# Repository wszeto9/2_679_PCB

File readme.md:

# 2.679/2.007 Carrier Board
High Power throughput board for the 2.007 "Legacy" Robotics Competiton @ MIT, Spring 2022

[Interactive BOM](https://htmlpreview.github.io/?https://raw.githubusercontent.com/wszeto9/2_679_PCB/main/bom/ibom.html)

<h2> Features:</h2>
<ul>
<li>20A socketable fused input</li>
<li>Reverse polarity protection with warning lights and buzzer to alert incorrect wiring</li>
<li>9V USB-C Power Delivery Input to run off larger battery packs during testing</li>
<li>Protection Circuit to prevent USB-C from backcharging battery</li>
<li>Motor headers with 8.2V Output</li>
<li>Adjustable Servo voltage from 5V to Battery voltage</li>
<li>6A Syncronous Buck converter to reduce the voltage difference between the servo voltage and battery boltage</li>
<li>16 Actuator Ports (8 individually controllable)</li>
<li>Comparator Circuit for light based start signal, directly wired to an Arduino Interrupt</li>
<li>Mechanically Adjustable trigger point for photoresistor interrupt input</li>
<li>8-channel RC controller input for compatability with Gobilda RC Receiver</li>
<li>MPU6050 and LSM6DS33 Header for heading measurements with interrupt pins connected to D2</li>
<li> 5V and 3.3V I2C headers for a multitude of sensor inputs</li>
<li>ARGB Debugging LEDs to offer more variations of debugging signals</li>
<li>ARGB Header to decorate robot in <i><b>light</b></i></li>
<li>Breakout boards for Hall Effect Sensors, In-Line current sensors, and I/O Breakout boards </li>
<li>Fun Silkscreen messages for my favorite professors </li>
</ul>

PCBA

Top

Top Unpopulated Board

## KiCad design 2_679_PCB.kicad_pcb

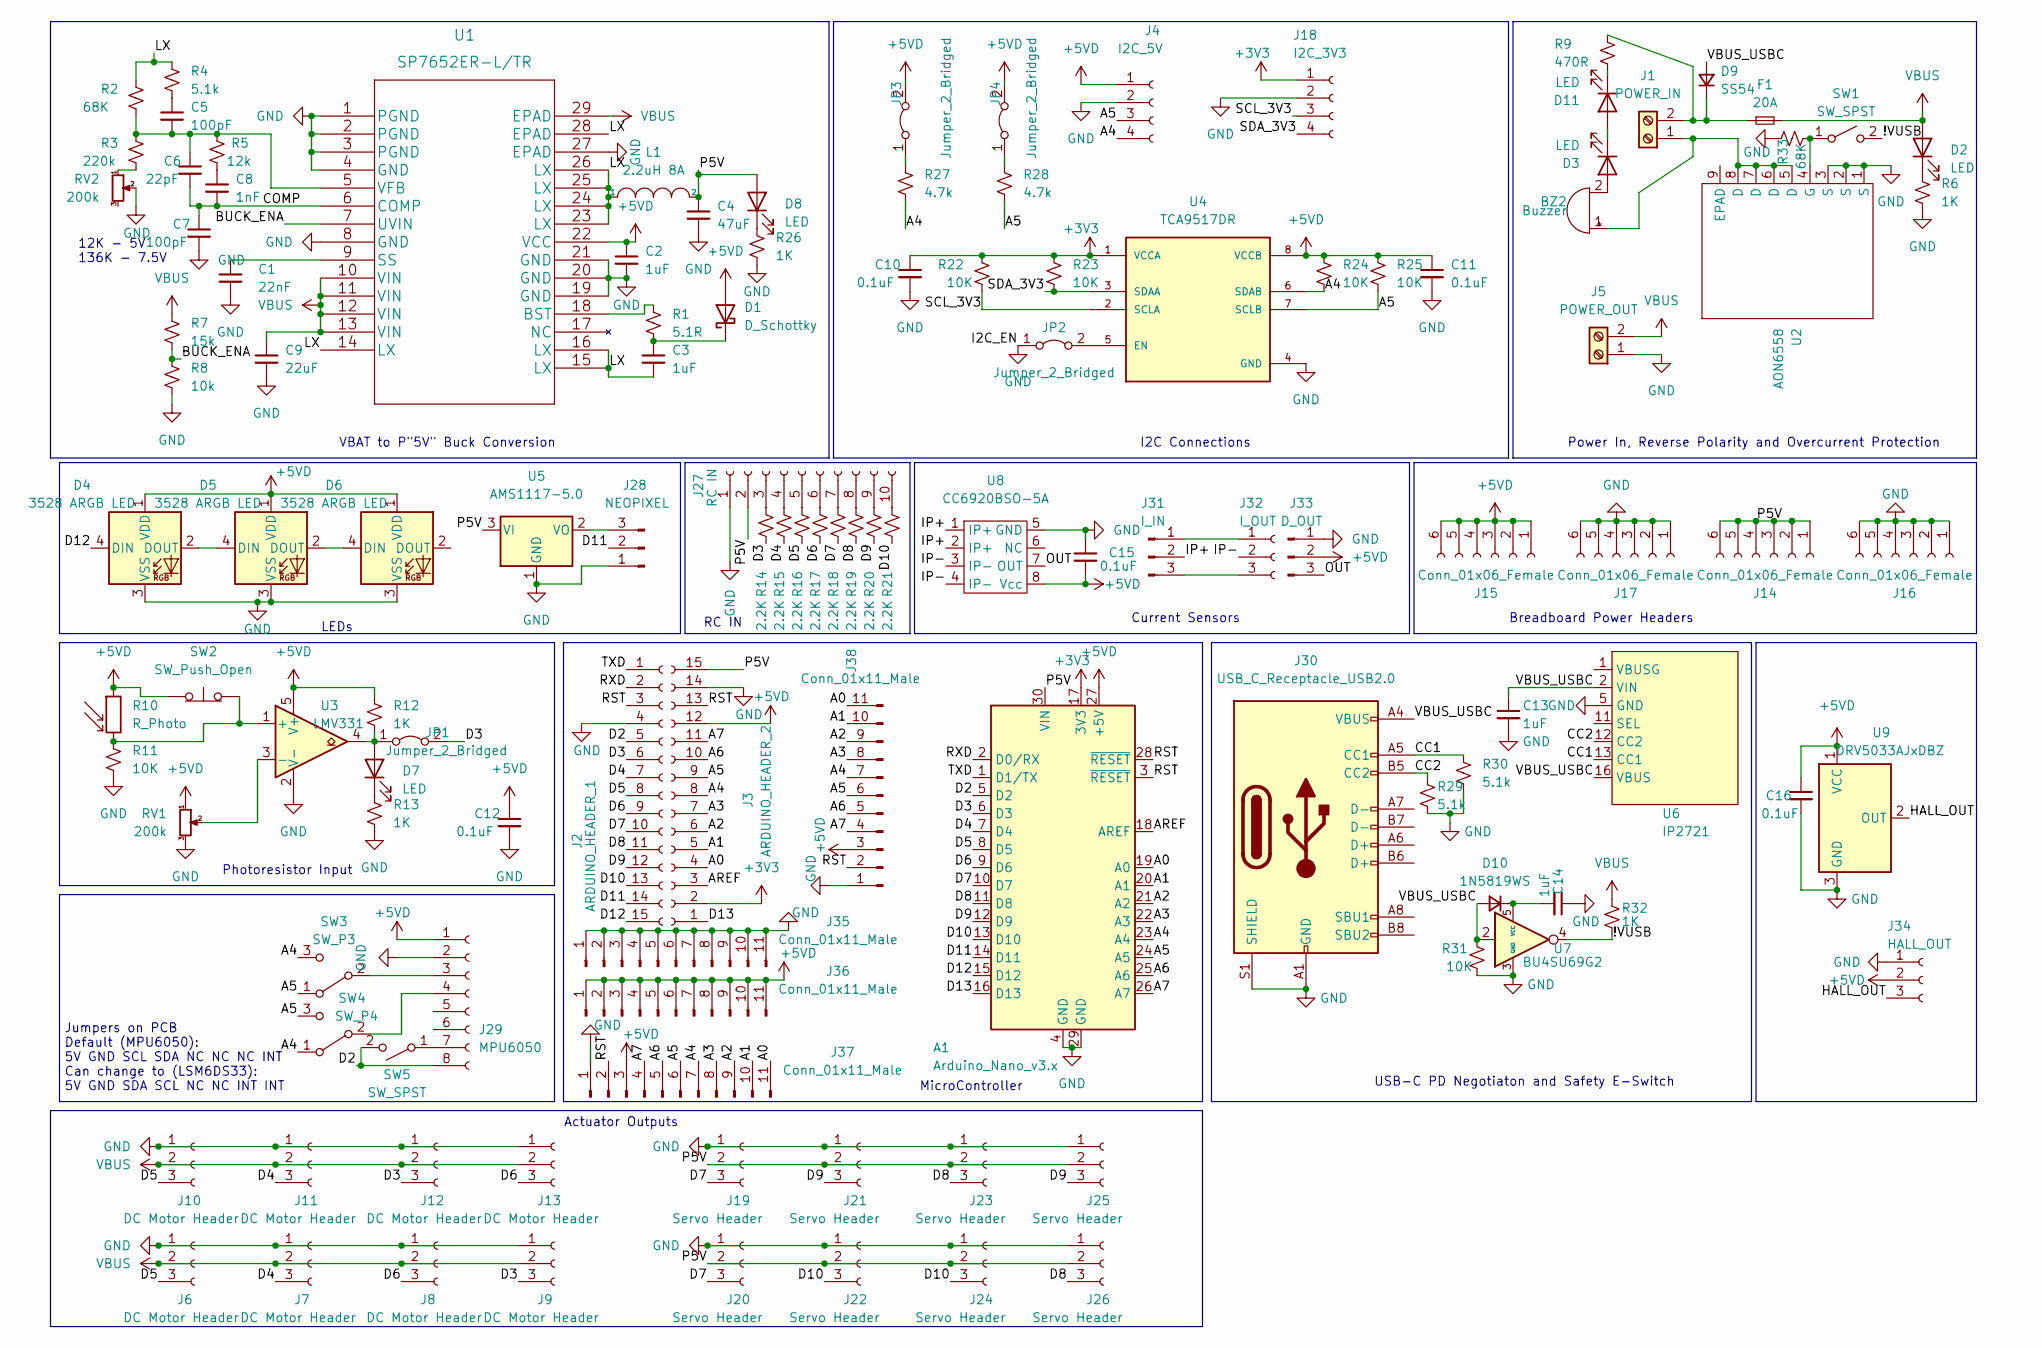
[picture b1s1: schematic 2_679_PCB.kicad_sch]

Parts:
A1: Arduino_Nano_v3.x; Arduino_Nano; Digikey 1738-1026-ND
BZ2: Buzzer; CP_Radial_D10.0mm_P5.00mm; Digikey 668-1454-ND
C1: 22nF; C_0402_1005Metric; LCSC C1532
C2, C3, C13, C14: 1uF; C_0402_1005Metric; LCSC C52923
C4: 47uF; C_1206_3216Metric; LCSC C96123
C5, C7: 100pF; C_0402_1005Metric; LCSC C1546
C6: 22pF; C_0402_1005Metric; LCSC C1555
C8: 1nF; C_0402_1005Metric; LCSC C1523
C9: 22uF; C_0805_2012Metric; LCSC C45783
C10, C11, C12, C15, C16: 0.1uF; C_0402_1005Metric; LCSC C307331
D1: D_Schottky; D_0402_1005Metric; Digikey 641-1272-1-ND
D2: LED; LED_0603_1608Metric; LCSC C2290
D3, D11: LED; LED_0603_1608Metric; LCSC C2286
D4, D5, D6: 3528 ARGB LED; LED_Cree-PLCC4_3.2x2.8mm_CCW; Digikey 2007-BB-HRGB32M-TRB-CCT-ND
D7: LED; LED_0603_1608Metric; LCSC C72043
D8: LED; LED_0603_1608Metric; LCSC C72038
D9: SS54; D_SMA; LCSC C22452
D10: 1N5819WS; D_SOD-323; LCSC C191023
F1: 20A; Fuseholder_Blade_Mini_Keystone_3568; Digikey 36-3568-ND
J1: POWER_IN; TerminalBlock_Phoenix_MKDS-1,5-2_1x02_P5.00mm_Horizontal; Digikey 796949-2-ND
J2: ARDUINO_HEADER_1; PinSocket_1x15_P2.54mm_Vertical; Digikey S7013-ND
J3: ARDUINO_HEADER_2; PinSocket_1x15_P2.54mm_Vertical; Digikey S7013-ND
J4: I2C_5V; PinSocket_1x04_P2.54mm_Vertical; Digikey S7002-ND
J5: POWER_OUT; TerminalBlock_Phoenix_MKDS-1,5-2-5.08_1x02_P5.08mm_Horizont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; Digikey 796949-2-ND
J6, J7, J8, J9, J10, J11, J12, J13: DC Motor Header; PinSocket_1x03_P2.54mm_Vertical; Digikey S7036-ND
J14, J15, J16, J17: Conn_01x06_Female; PinSocket_1x06_P2.54mm_Vertical; Digikey S7004-ND
J18: I2C_3V3; PinSocket_1x04_P2.54mm_Vertical; Digikey S7002-ND
J19, J20, J21, J22, J23, J24, J25, J26: Servo Header; PinSocket_1x03_P2.54mm_Vertical; Digikey S7036-ND
J27: RC IN; PinSocket_1x10_P2.54mm_Vertical; Digikey S7043-ND
J28: NEOPIXEL; PinHeader_1x03_P2.54mm_Vertical; Digikey S7036-ND
J29: MPU6050; PinHeader_1x08_P2.54mm_Vertical; Digikey S7006-ND
J30: USB_C_Receptacle_USB2.0; USB_C_Receptacle_Palconn_UTC16-G; Digikey 2073-USB4105-GF-ACT-ND
J31: I_IN; PinSocket_1x03_P2.54mm_Vertical; Digikey S7036-ND
J32: I_OUT; PinSocket_1x03_P2.54mm_Vertical; Digikey S7036-ND
J33: D_OUT; PinSocket_1x03_P2.54mm_Vertical; Digikey S7036-ND
J34: HALL_OUT; PinHeader_1x03_P2.54mm_Vertical_SMD_Pin1Left; Digikey S5595-ND
J35, J36, J37, J38: Conn_01x11_Male; PinHeader_1x11_P2.54mm_Vertical; Digikey S7009-ND
JP1, JP2: Jumper_2_Bridged; PinHeader_1x02_P2.54mm_Vertical
JP3, JP4: Jumper_2_Bridged; SolderJumper-2_P1.3mm_Bridged_Pad1.0x1.5mm
L1: 2.2uH 8A; L_Abracon_ASPI-0630LR; Digikey 308-2464-1-ND
R1: 5.1R; R_0603_1608Metric; LCSC C25197
R2, R33: 68K; R_0402_1005Metric; LCSC C36871
R3: 220k; R_0402_1005Metric; LCSC C25767
R4, R29, R30: 5.1k; R_0402_1005Metric; LCSC C25905
R5: 12k; R_0402_1005Metric; LCSC C25752
R6, R12, R13, R26, R32: 1K; R_0402_1005Metric; LCSC C11702
R7: 15k; R_0402_1005Metric; LCSC C25756
R8: 10k; R_0402_1005Metric; LCSC C25744
R9: 470R; R_0402_1005Metric; LCSC C25117
R10: R_Photo; PinSocket_1x02_P2.54mm_Vertical; Digikey S7000-ND
R11, R22, R23, R24, R25, R31: 10K; R_0402_1005Metric; LCSC C25744
R14, R15, R16, R17, R18, R19, R20, R21: 2.2K; R_0402_1005Metric; LCSC C25879
R27, R28: 4.7k; R_0402_1005Metric; LCSC C25900
RV1, RV2: 200k; Potentiometer_Bourns_TC33X_Vertical; Digikey TC33X-2-204ECT-ND
SW1: SW_SPST; M2012SS2W13; Digikey 360-2840-ND
SW2: SW_Push_Open; SW_SPST_CK_RS282G05A3; Digikey CKN12326-1-ND
SW3: SW_P3; SolderJumper-3_P1.3mm_Bridged12_Pad1.0x1.5mm
SW4: SW_P4; SolderJumper-3_P1.3mm_Bridged12_Pad1.0x1.5mm
SW5: SW_SPST; SolderJumper-2_P1.3mm_Open_TrianglePad1.0x1.5mm; Digikey 360-2840-ND
U1: SP7652ER-L/TR; SP7652ER-L&slash_TR; Digikey 1016-1843-1-ND
U2: AON6558; DFN-8-1EP_6x5mm_P1.27mm_EP4x4mm; Digikey 785-1670-1-ND
U3: LMV331; SOT-23-5; Digikey LMV331M5X/NOPBCT-ND
U4: TCA9517DR; SOIC127P599X175-8N; PARTREV D
U5: AMS1117-5.0; SOT-223-3_TabPin2
U6: IP2721; TSSOP-16_4.4x5mm_P0.65mm
U7: BU4SU69G2; SOT-23-5; Digikey BU4SU69G2CT-ND
U8: CC6920BSO-5A; SOP-8_3.9x4.9mm_P1.27mm; LCSC C2880430
U9: DRV5033AJxDBZ; SOT-23

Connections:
+3V3: A1.17 (3V3), C10.1, J3.2, J18.1, R22.1, R23.1, U4.1 (VCCA)
+5VD: A1.27 (+5V), C2.1, C11.1, C12.1, C15.2, C16.1, D1.2 (A), D4.1 (VDD), D5.1 (VDD), D6.1 (VDD), J3.12, J4.1, J15.1, J15.2, J15.3, J15.4, J15.5, J15.6, J29.1, J33.2, J34.2, J36.1, J36.2, J36.3, J36.4, J36.5, J36.6, J36.7, J36.8, J36.9, J36.10, J36.11, J37.3, J38.3, JP3.2 (B), JP4.2 (B), R10.1, R12.1, R24.1, R25.1, RV1.1, SW2.1 (A), U1.22 (VCC), U3.5 (V+), U4.8 (VCCB), U8.8 (Vcc), U9.1 (VCC)
/!VUSB: R32.2, SW1.2 (B), U7.4
/A0: A1.19 (A0), J3.4, J37.11, J38.11
/A1: A1.20 (A1), J3.5, J37.10, J38.10
/A2: A1.21 (A2), J3.6, J37.9, J38.9
/A3: A1.22 (A3), J3.7, J37.8, J38.8
/A4: A1.23 (A4), J3.8, J4.4, J37.7, J38.7, R24.2, R27.2, SW3.3 (C), SW4.1 (A), U4.6 (SDAB)
/A5: A1.24 (A5), J3.9, J4.3, J37.6, J38.6, R25.2, R28.2, SW3.1 (A), SW4.3 (C), U4.7 (SCLB)
/A6: A1.25 (A6), J3.10, J37.5, J38.5
/A7: A1.26 (A7), J3.11, J37.4, J38.4
/AREF: A1.18 (AREF), J3.3
/BUCK_ENA: R7.2, R8.1, U1.7 (UVIN)
/CC1: J30.A5 (CC1), R30.1, U6.13 (CC1)
/CC2: J30.B5 (CC2), R29.1, U6.12 (CC2)
/COMP: C6.2, C7.1, C8.2, U1.6 (COMP)
/D2: A1.5 (D2), J2.5, J29.8, SW5.2 (B)
/D3: A1.6 (D3), J2.6, J9.3, J12.3, JP1.2 (B), R14.1
/D4: A1.7 (D4), J2.7, J7.3, J11.3, R15.1
/D5: A1.8 (D5), J2.8, J6.3, J10.3, R16.1
/D6: A1.9 (D6), J2.9, J8.3, J13.3, R17.1
/D7: A1.10 (D7), J2.10, J19.3, J20.3, R18.1
/D8: A1.11 (D8), J2.11, J23.3, J26.3, R19.1
/D9: A1.12 (D9), J2.12, J21.3, J25.3, R20.1
/D10: A1.13 (D10), J2.13, J22.3, J24.3, R21.1
/D11: A1.14 (D11), J2.14, J28.2
/D12: A1.15 (D12), D4.4 (DIN), J2.15
/D13: A1.16 (D13), J3.1
/HALL_OUT: J34.3, U9.2 (OUT)
/IP+: J31.2, U8.1 (IP+), U8.2 (IP+)
/IP-: J32.2, U8.3 (IP-), U8.4 (IP-)
/LX: C3.2, L1.1, R2.2, R4.1, U1.14 (LX), U1.15 (LX), U1.16 (LX), U1.23 (LX), U1.24 (LX), U1.25 (LX), U1.26 (LX), U1.28 (EPAD)
/OUT: J33.3, U8.7 (OUT)
/P5V: A1.30 (VIN), C4.1, D8.2 (A), J3.15, J14.1, J14.2, J14.3, J14.4, J14.5, J14.6, J19.2, J20.2, J21.2, J22.2, J23.2, J24.2, J25.2, J26.2, J27.2, L1.2, U5.3 (VI)
/RST: A1.3 (~RESET), A1.28 (~RESET), J2.3, J3.13, J37.2, J38.2
/RXD: A1.2 (D0/RX), J2.2
/SCL_3V3: J18.3, R22.2, U4.2 (SCLA)
/SDA_3V3: J18.4, R23.2, U4.3 (SDAA)
/TXD: A1.1 (D1/TX), J2.1
/VBUS_USBC: C13.1, D9.2 (A), D10.2 (A), J30.A4 (VBUS), J30.A9 (VBUS), J30.B4 (VBUS), J30.B9 (VBUS), R31.1, U6.2 (VIN), U6.16 (VBUS), U7.2
GND: A1.4 (GND), A1.29 (GND), C1.2, C2.2, C4.2, C7.2, C9.2, C10.2, C11.2, C12.2, C13.2, C14.1, C15.1, C16.2, D4.3 (VSS), D5.3 (VSS), D6.3 (VSS), J2.4, J3.14, J4.2, J5.1, J6.1, J7.1, J8.1, J9.1, J10.1, J11.1, J12.1, J13.1, J16.1, J16.2, J16.3, J16.4, J16.5, J16.6, J17.1, J17.2, J17.3, J17.4, J17.5, J17.6, J18.2, J19.1, J20.1, J21.1, J22.1, J23.1, J24.1, J25.1, J26.1, J27.1, J28.1, J29.2, J30.A1 (GND), J30.A12 (GND), J30.B1 (GND), J30.B12 (GND), J30.S1 (SHIELD), J33.1, J34.1, J35.1, J35.2, J35.3, J35.4, J35.5, J35.6, J35.7, J35.8, J35.9, J35.10, J35.11, J37.1, J38.1, JP2.1 (A), R6.2, R8.2, R11.2, R13.2, R26.2, R29.2, R30.2, R31.2, R33.2, RV1.3, RV2.2, U1.1 (PGND), U1.2 (PGND), U1.3 (PGND), U1.4 (GND), U1.8 (GND), U1.19 (GND), U1.20 (GND), U1.21 (GND), U1.27 (EPAD), U2.1 (S), U2.2 (S), U2.3 (S), U3.2 (V-), U4.4 (GND), U5.1 (GND), U6.5 (GND), U7.3 (GND), U8.5 (GND), U9.3 (GND)
unnamed: BZ2.1 (-), J1.1, U2.5 (D), U2.6 (D), U2.7 (D), U2.8 (D)
unnamed: BZ2.2 (+), D3.2 (A)
unnamed: C1.1, U1.9 (SS)
unnamed: C3.1, D1.1 (K), R1.2
unnamed: C5.1, R4.2
unnamed: C5.2, C6.1, R2.1, R3.2, R5.1, U1.5 (VFB)
unnamed: C8.1, R5.2
unnamed: C14.2, D10.1 (K), U7.5 (VCC)
unnamed: D2.1 (K), R6.1
unnamed: D4.2 (DOUT), D5.4 (DIN)
unnamed: D5.2 (DOUT), D6.4 (DIN)
unnamed: D7.1 (K), R13.1
unnamed: D7.2 (A), JP1.1 (A), R12.2, U3.4
unnamed: D8.1 (K), R26.1
unnamed: D9.1 (K), F1.1, J1.2, R9.2
unnamed: D11.1 (K), R9.1
unnamed: D3.1 (K), D11.2 (A)
unnamed: J27.3, R14.2
unnamed: J27.4, R15.2
unnamed: J27.5, R16.2
unnamed: J27.6, R17.2
unnamed: J27.7, R18.2
unnamed: J27.8, R19.2
unnamed: J27.9, R20.2
unnamed: J27.10, R21.2
unnamed: J28.3, U5.2 (VO)
unnamed: J29.3, SW3.2 (B)
unnamed: J29.4, SW4.2 (B)
unnamed: J29.7, SW5.1 (A)
unnamed: J31.1, J32.1
unnamed: J31.3, J32.3
unnamed: JP2.2 (B), U4.5 (EN)
unnamed: JP3.1 (A), R27.1
unnamed: JP4.1 (A), R28.1
unnamed: R1.1, U1.18 (BST)
unnamed: R3.1, RV2.1
unnamed: R10.2, R11.1, SW2.2 (B), U3.1 (+)
unnamed: R33.1, SW1.1 (A), U2.4 (G)
unnamed: RV1.2, U3.3 (-)
VBUS: C9.1, D2.2 (A), F1.2, J5.2, J6.2, J7.2, J8.2, J9.2, J10.2, J11.2, J12.2, J13.2, R7.1, R32.1, U1.10 (VIN), U1.11 (VIN), U1.12 (VIN), U1.13 (VIN), U1.29 (EPAD)

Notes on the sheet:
Actuator Outputs
LEDs
Current Sensors
VBAT to P"5V" Buck Conversion
Jumpers on PCB Default (MPU6050): 5V GND SCL SDA NC NC NC INT Can change to (LSM6DS33): 5V GND SDA SCL NC NC INT INT
Power In, Reverse Polarity and Overcurrent Protection
MicroController
Breadboard Power Headers
USB-C PD Negotiaton and Safety E-Switch
RC IN
Photoresistor Input
I2C Connections
12K - 5V 136K - 7.5V

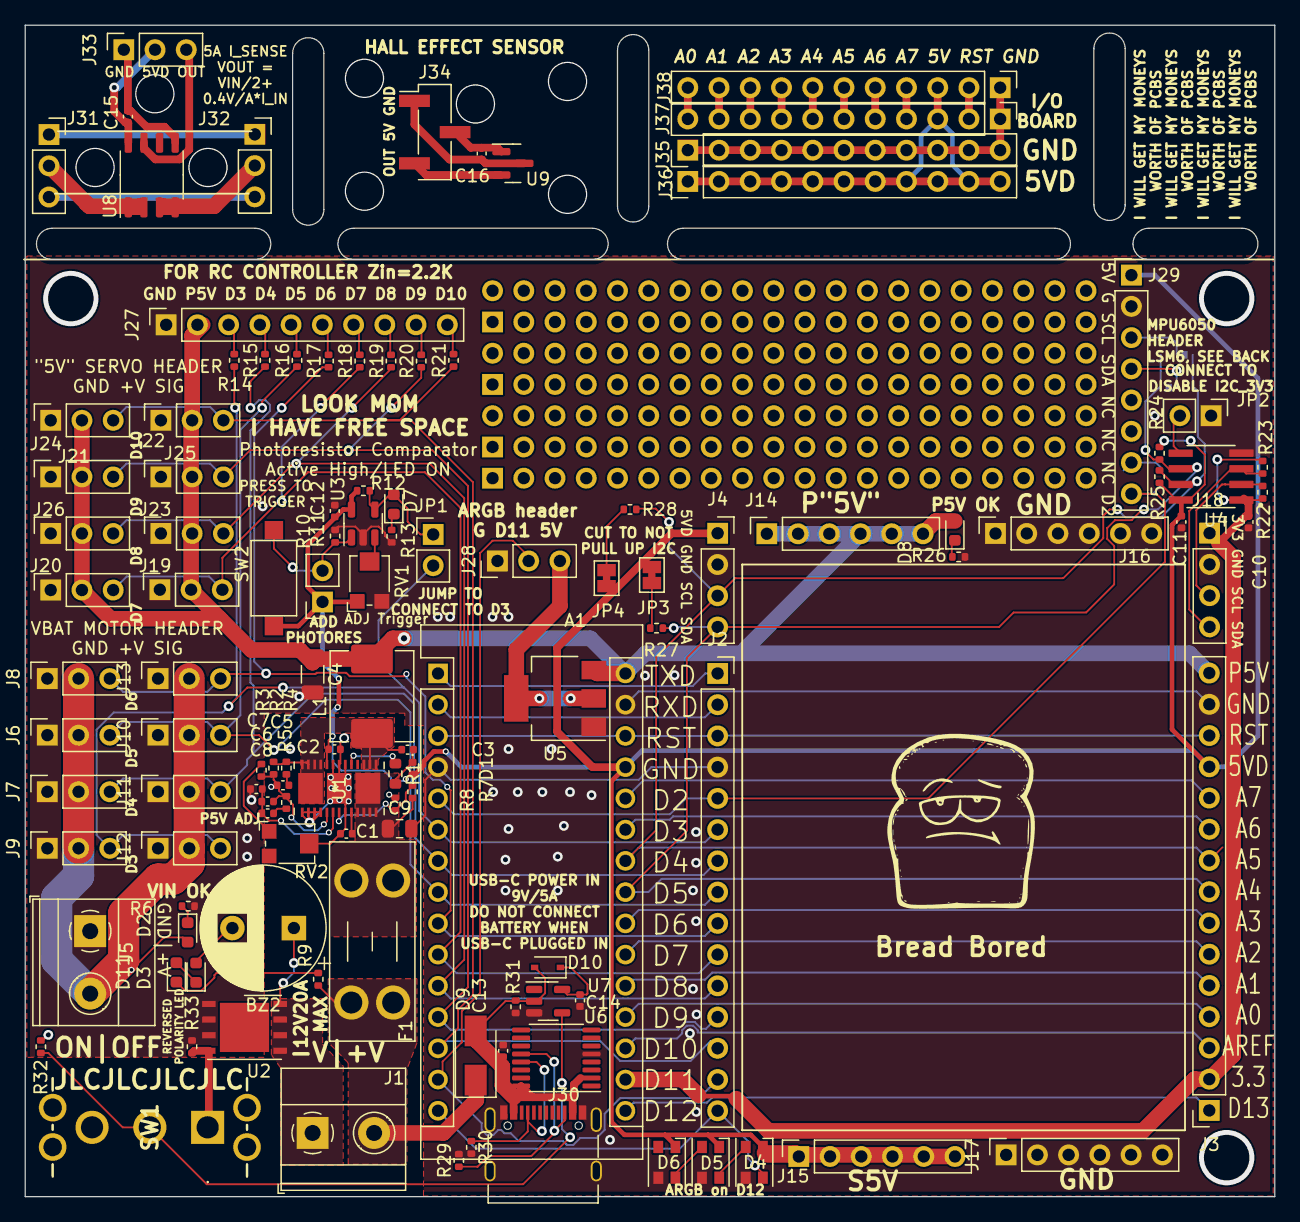
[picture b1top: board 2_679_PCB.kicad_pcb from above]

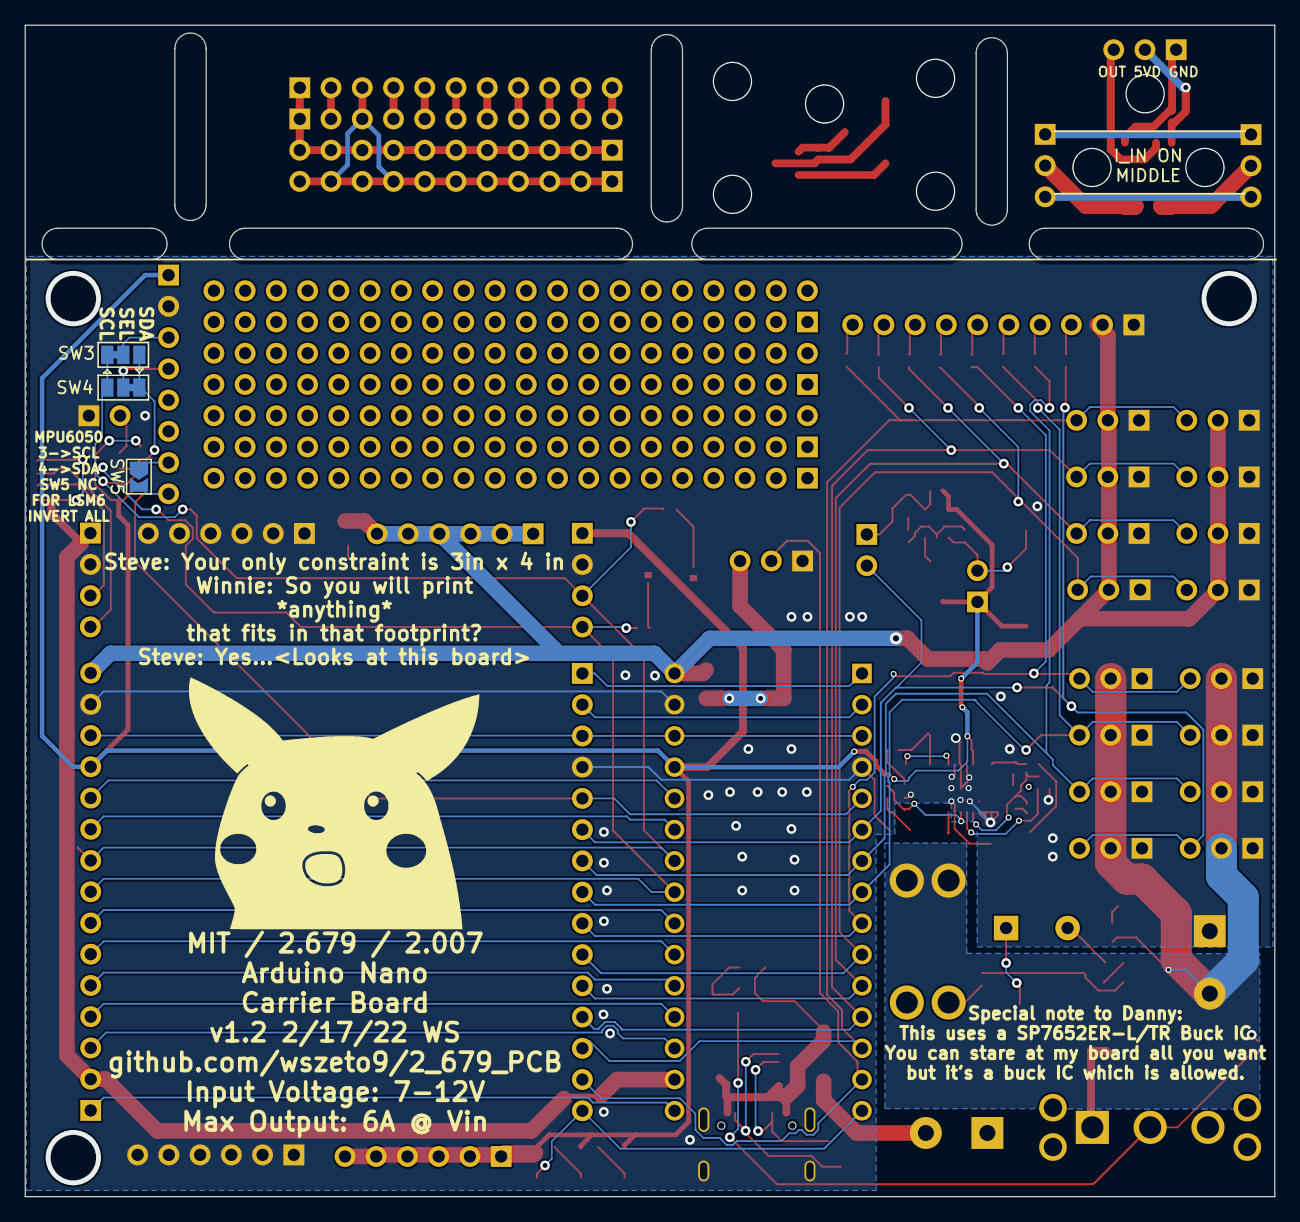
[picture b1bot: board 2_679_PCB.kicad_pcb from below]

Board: 2 copper layers, 101.6 x 95.2 mm, 122 parts (3 on the bottom side), 81 nets.

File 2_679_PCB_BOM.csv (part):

"Source:","C:\Users\Winnie\Documents\Classwork\S22\2.679\PCB\2_679_PCB\2_679_PCB.kicad_sch"
"Date:","3/15/2022 5:42:34 PM"
"Tool:","Eeschema (6.0.1)"
"Generator:","C:\Program Files\KiCad\6.0\bin\scripting\plugins/bom_csv_grouped_by_value.py"
"Component Count:","97"

"Individual Components:"

"Item","Qty","Reference(s)","Value","LibPart","Footprint","Datasheet","Digikey","LCSC","MANUFACTURER","MAXIMUM_PACKAGE_HEIGHT","PARTREV","STANDARD"
"","","A1","Arduino_Nano_v3.x","MCU_Module:Arduino_Nano_v3.x","Module:Arduino_Nano","http://www.mouser.com/pdfdocs/Gravitech_Arduino_Nano3_0.pdf","","","","","",""
"","","BZ2","Buzzer","Device:Buzzer","Capacitor_THT:CP_Radial_D10.0mm_P5.00mm","https://www.digikey.com/en/products/detail/pui-audio-inc/AI-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","668-1454-ND","","","","",""
"","","C1","22nF","Device:C_Small","Capacitor_SMD:C_0402_1005Metric","https://www.digikey.com/en/products/detail/kemet/C0402C223K5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","399-C0402C223K5REC7411CT-ND","C1532","","","",""
"","","C2","1uF","Device:C_Small","Capacitor_SMD:C_0402_1005Metric","https://www.digikey.com/en/products/detail/samsung-electro-m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","1276-1067-1-ND","C52923","","","",""
"","","C3","1uF","Device:C_Small","Capacitor_SMD:C_0402_1005Metric","https://www.digikey.com/en/products/detail/samsung-electro-m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","1276-1067-1-ND","C52923","","","",""
"","","C4","47uF","Device:C_Small","Capacitor_SMD:C_1206_3216Metric","~","","C96123","","","",""
"","","C5","100pF","Device:C_Small","Capacitor_SMD:C_0402_1005Metric","https://www.digikey.com/en/products/detail/yageo/CC0402JRNPO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","311-1024-1-ND","C1546","","","",""
"","","C6","22pF","Device:C_Small","Capacitor_SMD:C_0402_1005Metric","https://www.digikey.com/en/products/detail/yageo/CC0402JRNPO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","311-1018-1-ND","C1555","","","",""
"","","C7","100pF","Device:C_Small","Capacitor_SMD:C_0402_1005Metric","https://www.digikey.com/en/products/detail/yageo/CC0402JRNPO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","311-1024-1-ND","C1546","","","",""
"","","C8","1nF","Device:C_Small","Capacitor_SMD:C_0402_1005Metric","https://www.digikey.com/en/products/detail/kemet/C0402C102J1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","399-C0402C102J1GEC7411CT-ND","C1523","","","",""
"","","C9","22uF","Device:C_Small","Capacitor_SMD:C_0805_2012Metric","~","","C45783","","","",""
"","","C10","0.1uF","Device:C_Small","Capacitor_SMD:C_0402_1005Metric","https://www.digikey.com/en/products/detail/murata-electronic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","490-3160-1-ND","C307331","","","",""
"","","C11","0.1uF","Device:C_Small","Capacitor_SMD:C_0402_1005Metric","https://www.digikey.com/en/products/detail/murata-electronic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","490-3160-1-ND","C307331","","","",""
"","","C12","0.1uF","Device:C_Small","Capacitor_SMD:C_0402_1005Metric","https://www.digikey.com/en/products/detail/murata-electronic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","490-3160-1-ND","C307331","","","",""
"","","D1","D_Schottky","Device:D_Schottky","Diode_SMD:D_0402_1005Metric","https://www.digikey.com/en/products/detail/comchip-technolog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","641-1272-1-ND","","","","",""
"","","D2","LED","Device:LED","LED_SMD:LED_0603_1608Metric","~","","C2290","","","",""
"","","D3","LED","Device:LED","LED_SMD:LED_0603_1608Metric","~","","C2286","","","",""
"","","D4","3528 ARGB LED","LED:SK6812MINI","LED_SMD:LED_Cree-PLCC4_3.2x2.8mm_CCW","https://www.digikey.com/en/products/detail/american-bright-o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","2007-BB-HRGB32M-TRB-CCT-ND","","","","",""
"","","D5","3528 ARGB LED","LED:SK6812MINI","LED_SMD:LED_Cree-PLCC4_3.2x2.8mm_CCW","https://www.digikey.com/en/products/detail/american-bright-o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","2007-BB-HRGB32M-TRB-CCT-ND","","","","",""
"","","D6","3528 ARGB LED","LED:SK6812MINI","LED_SMD:LED_Cree-PLCC4_3.2x2.8mm_CCW","https://www.digikey.com/en/products/detail/american-bright-o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","2007-BB-HRGB32M-TRB-CCT-ND","","","","",""
"","","D7","LED","Device:LED","LED_SMD:LED_0603_1608Metric","~","","C72043","","","",""
"","","D8","LED","Device:LED","LED_SMD:LED_0603_1608Metric","~","","C72038","","","",""
"","","F1","20A","Device:Fuse_Small","Fuse:Fuseholder_Blade_Mini_Keystone_3568","https://www.digikey.com/en/products/detail/keystone-electron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 ","36-3568-ND","","","","",""
"","","J1","POWER_IN","Connector:Screw_Terminal_01x02","TerminalBlock_Phoenix:TerminalBlock_Phoenix_MKDS-1,5-2_1x02_P5.00mm_Horizontal","https://www.digikey.com/en/products/detail/te-connectivity-a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","796949-2-ND","","","","",""
"","","J2","ARDUINO_HEADER_1","Connector:Conn_01x15_Female","Connector_PinSocket_2.54mm:PinSocket_1x15_P2.54mm_Vertical","https://www.digikey.com/en/products/detail/sullins-connector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","S7013-ND","","","","",""
"","","J3","ARDUINO_HEADER_2","Connector:Conn_01x15_Female","Connector_PinSocket_2.54mm:PinSocket_1x15_P2.54mm_Vertical","https://www.digikey.com/en/products/detail/sullins-connector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","S7013-ND","","","","",""
"","","J4","I2C_5V","Connector:Conn_01x04_Female","Connector_PinSocket_2.54mm:PinSocket_1x04_P2.54mm_Vertical","https://www.digikey.com/en/products/detail/sullins-connector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","S7002-ND","","","","",""
"","","J5","POWER_OUT","Connector:Screw_Terminal_01x02","TerminalBlock_Phoenix:TerminalBlock_Phoenix_MKDS-1,5-2-5.08_1x02_P5.08mm_Horizontal","https://www.digikey.com/en/products/detail/te-connectivity-a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","796949-2-ND","","","","",""
"","","J6","DC Motor Header","Connector:Conn_01x03_Female","Connector_PinSocket_2.54mm:PinSocket_1x03_P2.54mm_Vertical","https://www.digikey.com/en/products/detail/sullins-connector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","S7036-ND","","","","",""
"","","J7","DC Motor Header","Connector:Conn_01x03_Female","Connector_PinSocket_2.54mm:PinSocket_1x03_P2.54mm_Vertical","https://www.digikey.com/en/products/detail/sullins-connector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","S7036-ND","","","","",""
"","","J8","DC Motor Header","Connector:Conn_01x03_Female","Connector_PinSocket_2.54mm:PinSocket_1x03_P2.54mm_Vertical","https://www.digikey.com/en/products/detail/sullins-connector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","S7036-ND","","","","",""
"","","J9","DC Motor Header","Connector:Conn_01x03_Female","Connector_PinSocket_2.54mm:PinSocket_1x03_P2.54mm_Vertical","https://www.digikey.com/en/products/detail/sullins-connector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","S7036-ND","","","","",""
"","","J10","DC Motor Header","Connector:Conn_01x03_Female","Connector_PinSocket_2.54mm:PinSocket_1x03_P2.54mm_Vertical","https://www.digikey.com/en/products/detail/sullins-connector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","S7036-ND","","","","",""
"","","J11","DC Motor Header","Connector:Conn_01x03_Female","Connector_PinSocket_2.54mm:PinSocket_1x03_P2.54mm_Vertical","https://www.digikey.com/en/products/detail/sullins-connector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","S7036-ND","","","","",""
"","","J12","DC Motor Header","Connector:Conn_01x03_Female","Connector_PinSocket_2.54mm:PinSocket_1x03_P2.54mm_Vertical","https://www.digikey.com/en/products/detail/sullins-connector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","S7036-ND","","","","",""
"","","J13","DC Motor Header","Connector:Conn_01x03_Female","Connector_PinSocket_2.54mm:PinSocket_1x03_P2.54mm_Vertical","https://www.digikey.com/en/products/detail/sullins-connector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","S7036-ND","","","","",""
"","","J14","Conn_01x06_Female","Connector:Conn_01x06_Female","Connector_PinSocket_2.54mm:PinSocket_1x06_P2.54mm_Vertical","~https://www.digikey.com/en/products/detail/sullins-connector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","S7004-ND","","","","",""
"","","J15","Conn_01x06_Female","Connector:Conn_01x06_Female","Connector_PinSocket_2.54mm:PinSocket_1x06_P2.54mm_Vertical","~https://www.digikey.com/en/products/detail/sullins-connector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","S7004-ND","","","","",""
"","","J16","Conn_01x06_Female","Connector:Conn_01x06_Female","Connector_PinSocket_2.54mm:PinSocket_1x06_P2.54mm_Vertical","~https://www.digikey.com/en/products/detail/sullins-connector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","S7004-ND","","","","",""
"","","J17","Conn_01x06_Female","Connector:Conn_01x06_Female","Connector_PinSocket_2.54mm:PinSocket_1x06_P2.54mm_Vertical","~https://www.digikey.com/en/products/detail/sullins-connector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","S7004-ND","","","","",""
"","","J18","I2C_3V3","Connector:Conn_01x04_Female","Connector_PinSocket_2.54mm:PinSocket_1x04_P2.54mm_Vertical","https://www.digikey.com/en/products/detail/sullins-connector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","S7002-ND","","","","",""
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
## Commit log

2022-03-16 fully defined states for inverter
2022-03-16 changed e-pads
    changed e-pads
2022-03-16 Doubled reverse bias LEDs
    Prevents LEDs from blowing up from 5V max reverse bias
2022-03-16 fixed DRC
    trace was routed incorrectly
2022-03-16 updated zip
2022-03-17 added breakout boards
    Added boards to increase space use of the board to 4x4"
2022-03-17 added documentation
2022-03-19 updated BOM
2022-03-20 added usb-c digikey part number
2022-03-28 added iBOM
2022-04-02 added arduino board and power distribution
2022-04-04 added power management board
2022-04-04 moved images
2022-04-04 moved photos
2022-07-10 added step files

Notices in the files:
parts and their libraries:
Copyright 2021 Accelerated Designs. All rights reserved.
